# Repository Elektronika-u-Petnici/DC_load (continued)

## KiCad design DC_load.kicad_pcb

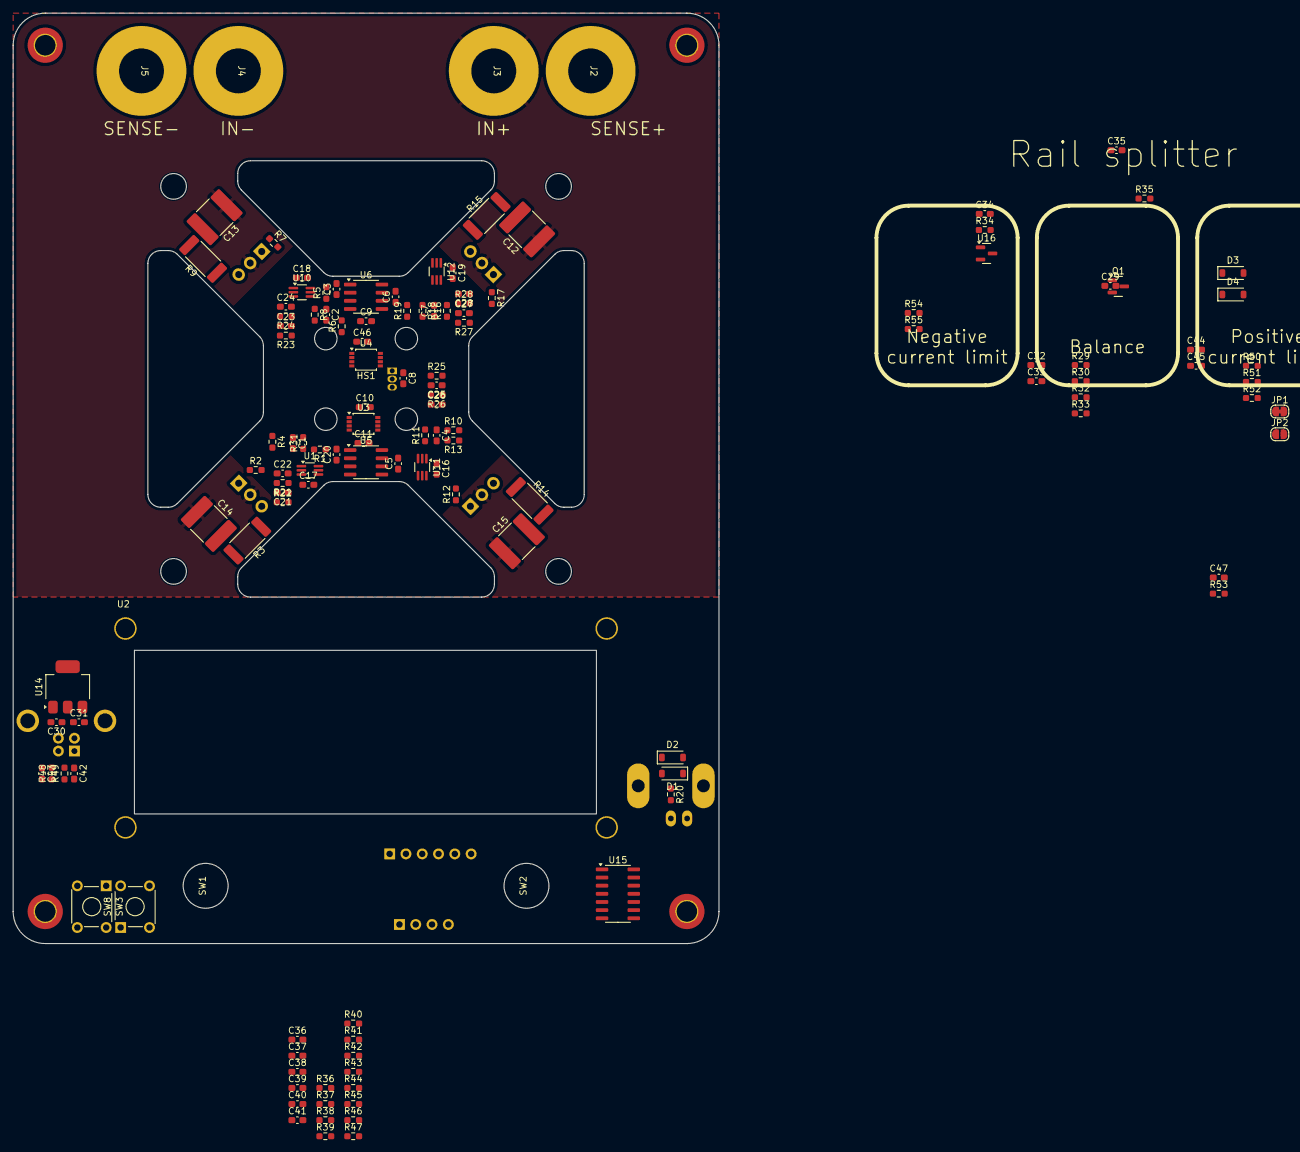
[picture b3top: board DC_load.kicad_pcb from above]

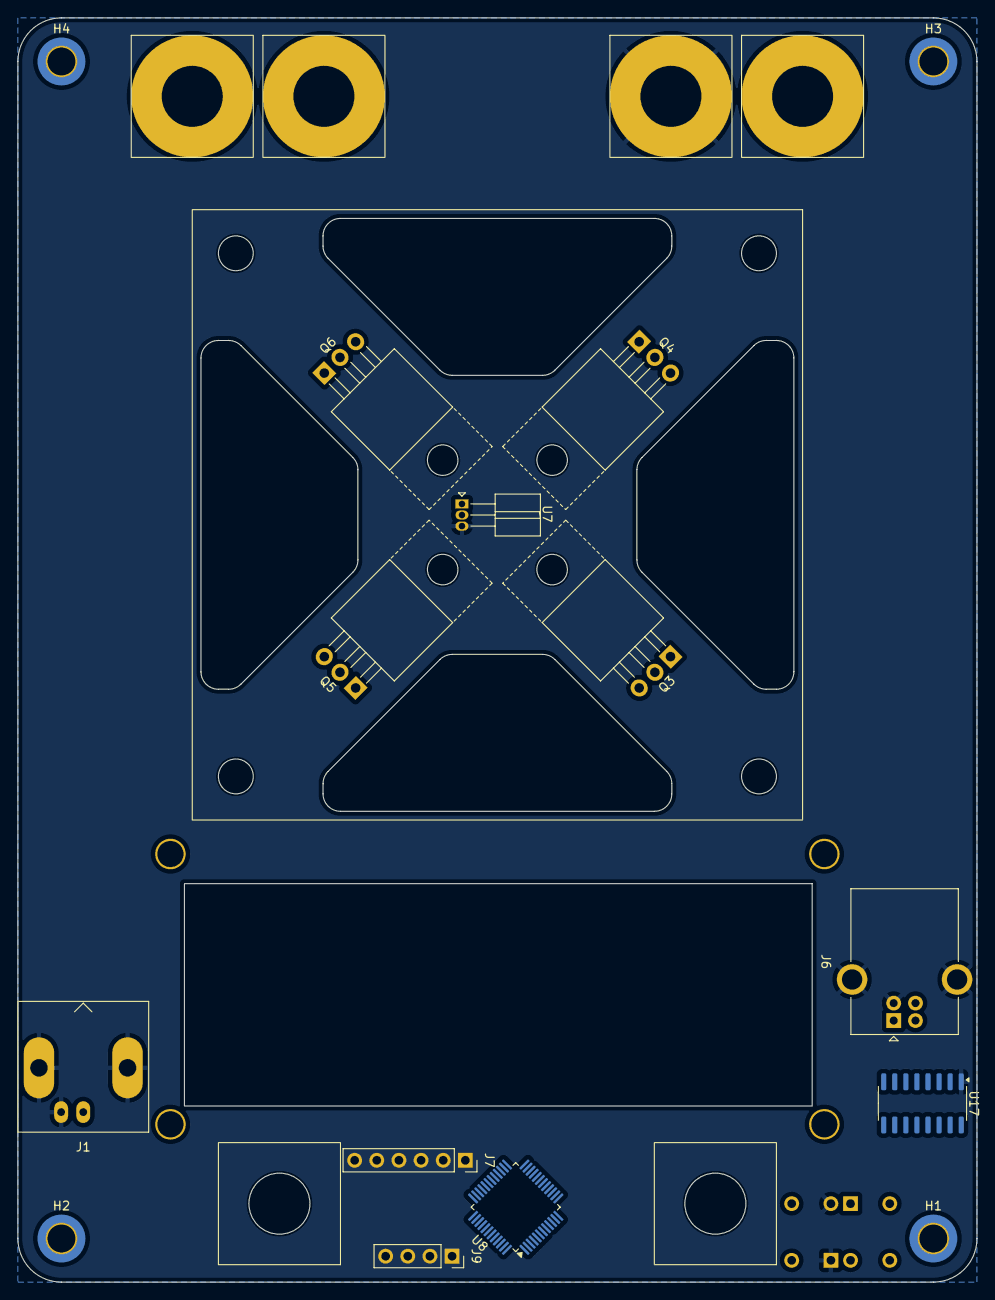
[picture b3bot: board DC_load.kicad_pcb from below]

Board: 2 copper layers, 110.0 x 145.0 mm, 145 parts (15 on the bottom side), 87 nets, no tracks yet.

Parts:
C1, C2, C3, C4, C5, C6, C7, C20, C22, C24, C26, C28: 100p; C_0603_1608Metric_Pad1.08x0.95mm_HandSolder
C8, C9, C10, C11, C16, C17, C18, C19, C29, C32, C33, C36, C39, C45, C46, C47: 100n; C_0603_1608Metric_Pad1.08x0.95mm_HandSolder
C12, C13, C14, C15: 1u; C_2220_5750Metric_Pad1.97x5.40mm_HandSolder
C21, C23, C25, C27, C37, C38, C40, C41, C44: 10n; C_0603_1608Metric_Pad1.08x0.95mm_HandSolder
C30, C31, C34, C35: 10u; C_0603_1608Metric_Pad1.08x0.95mm_HandSolder
C42, C43: 47p; C_0603_1608Metric_Pad1.08x0.95mm_HandSolder
D1, D2, D3, D4: 1N4148W; D_SOD-123
H1, H2, H3, H4: MountingHole; M3_hole_with_spacer
HS1: Heatsink; AMD_heatsink
J1: Conn_Coaxial; BNC_Amphenol_B6252HB-NPP3G-50_Horizontal
J2: red_terminal; 4mm_terminal_red
J3: red terminal; 4mm_terminal_red
J4, J5: black terminal; 4mm_terminal_black
J6: USB_B; USB_B_OST_USB-B1HSxx_Horizontal
J7: Conn_01x06_Socket; PinSocket_1x06_P2.54mm_Vertical
J9: Conn_01x04_Socket; PinSocket_1x04_P2.54mm_Vertical
JP1: Jumper_2_Bridged; SolderJumper-2_P1.3mm_Bridged_RoundedPad1.0x1.5mm
JP2: Jumper_2_Open; SolderJumper-2_P1.3mm_Open_RoundedPad1.0x1.5mm
Q1: MMBT5401; SOT-23
Q3, Q4, Q5, Q6: FQP19N20C; TO-220-3_Horizontal_TabUp
R1, R2, R7, R8, R12, R13, R16, R17, R20, R22, R23, R25, R27, R34, R35, R50, R52: 100; R_0603_1608Metric_Pad0.98x0.95mm_HandSolder
R3, R9, R14, R15: 10 mOhm; R_2512_6332Metric_Pad1.40x3.35mm_HandSolder
R4, R5, R6, R10, R11, R18, R19, R21, R24, R26, R28, R31, R36, R37, R39, R41, R43, R45, R51, R53, R54, R55: 10k; R_0603_1608Metric_Pad0.98x0.95mm_HandSolder
R29, R32: 1Meg; R_0603_1608Metric_Pad0.98x0.95mm_HandSolder
R30, R33: 50k; R_0603_1608Metric_Pad0.98x0.95mm_HandSolder
R38, R40, R42, R44, R46, R47: 100k; R_0603_1608Metric_Pad0.98x0.95mm_HandSolder
R48, R49: 22; R_0603_1608Metric_Pad0.98x0.95mm_HandSolder
SW1, SW2: RotaryEncoder_Switch; rotary_encoder_bottom_solder
SW3, SW8: SW_Push; SW_TH_Tactile_Omron_B3F-10xx
U1, U10, U11, U12: FSA3157P6X; SOT-363_SC-70-6_Handsoldering
U2: Screen; WC1602A - below
U3, U4: NCS21802; OnSemi_Micro8
U5, U6: TLV9062; SOIC-8_3.9x4.9mm_P1.27mm
U7: LMT84LPM; TO-92_Inline_W4.0mm_Horizontal_FlatSideUp
U8: STM32F103C8Tx; LQFP-48_7x7mm_P0.5mm
U14: AMS1117-3.3; SOT-223-3_TabPin2
U15: 74HC14D653; SOIC-14_3.9x8.7mm_P1.27mm
U16: LM4040DBZ-3; SOT-23
U17: CH340C; SOIC-16_3.9x9.9mm_P1.27mm

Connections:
3V3: C9.2, C29.2, C30.1, C46.2, D2.1 (K), JP2.2 (B), U3.8 (V+), U4.8 (V+), U8.1 (VBAT), U8.24 (VDD), U8.36 (VDD), U8.48 (VDD), U14.2 (VO), U17.16 (VCC)
5V: C10.2, C11.2, C16.2, C17.2, C18.2, C19.2, U1.5 (V+), U5.8 (V+), U6.8 (V+), U10.5 (V+), U11.5 (V+), U12.5 (V+)
+3V3: J7.4, J9.2, R36.1, R37.1, R39.1, R41.1, R43.1, R45.1, R51.1, R54.1, R55.1, SW3.2
+5V: C8.1, C31.1, D4.2 (A), J6.1 (VBUS), R34.2, R35.2, U7.1 (+V_{S}), U14.3 (VI)
/Microcontroller/BNC_CONTROL: D1.1 (K), D2.2 (A), R20.1, U1.1, U10.1, U11.1, U12.1
/Microcontroller/CH1_MEAS: C20.1, R4.2, U5.2 (-), U8.10 (PA0)
/Microcontroller/CH2_MEAS: C2.1, R5.1, R6.2, U4.1, U8.11 (PA1)
/Microcontroller/CH3_MEAS: C5.1, R10.2, U5.6 (-), U8.14 (PA4)
/Microcontroller/CH4_MEAS: C7.1, R18.2, R19.1, U4.7, U8.18 (PB0)
/Microcontroller/TX2: R52.2, U8.12 (PA2)
/Power_stage/V_SENSE+: J2.1, R29.2
/Power_stage/V_SENSE-: J5.1, R32.2
BOOT: C47.2, R53.1, SW3.1, U8.44 (BOOT0)
CH1_CONTROL: U1.4, U5.3 (+)
CH1_PWM: U8.29 (PA8), U15.9
CH2_CONTROL: U6.3 (+), U10.4
CH2_PWM: U8.38 (PA15), U15.11
CH3_CONTROL: U5.5 (+), U11.4
CH3_PWM: U8.16 (PA6), U15.13
CH4_CONTROL: U6.5 (+), U12.4
CH4_PWM: U8.17 (PA7), U15.1
CTRL_SEL: U1.6, U10.6, U11.6, U12.6
ENC_A_1: C40.2, R44.2
ENC_A_2: C37.2, R40.2
ENC_B_1: C41.2, R47.2
ENC_B_2: C38.2, R46.2
ENC_SW_1: C39.2, R42.2
ENC_SW_2: C36.2, R38.2
GND: C8.2, C9.1, C10.1, C11.1, C12.2, C13.2, C14.2, C15.2, C16.1, C17.1, C18.1, C19.1, C21.1, C22.1, C23.1, C24.1, C25.1, C26.1, C27.1, C28.1, C29.1, C30.2, C31.2, C32.1, C33.1, C34.2, C35.2, C36.1, C37.1, C38.1, C39.1, C40.1, C41.1, C42.2, C43.2, C44.1, C45.1, C46.1, C47.1, D1.2 (A), J1.2 (Ext), J4.1, J6.4 (GND), J6.5 (Shield), J7.6, J9.1, R1.1, R3.2, R8.1, R9.2, R13.1, R14.2, R15.2, R16.1, R30.2, R53.2, SW8.1, U1.2 (GND), U3.4 (V-), U4.4 (V-), U5.4 (V-), U6.4 (V-), U7.3 (GND), U8.8 (VSSA), U8.23 (VSS), U8.35 (VSS), U8.47 (VSS), U10.2 (GND), U11.2 (GND), U12.2 (GND), U14.1 (GND), U15.3, U15.5, U15.7 (GND), U16.2 (A), U17.1 (GND)
INPUT_POWER: C12.1, C13.1, C14.1, C15.1, J3.1, Q3.2 (D), Q4.2 (D), Q5.2 (D), Q6.2 (D)
unnamed: C1.1, R4.1, R31.2, U3.1
unnamed: C3.2, R7.2, U6.1
unnamed: C4.1, R10.1, R11.2, U3.7
unnamed: C5.2, R12.2, U5.7
unnamed: C6.2, R17.2, U6.7
unnamed: C20.2, R2.2, U5.1
unnamed: C21.2, R21.2, R22.1
unnamed: C22.2, R21.1, U1.3
unnamed: C23.2, R23.1, R24.2
unnamed: C24.2, R24.1, U10.3
unnamed: C25.2, R25.1, R26.2
unnamed: C26.2, R26.1, U11.3
unnamed: C27.2, R27.1, R28.2
unnamed: C28.2, R28.1, U12.3
unnamed: D3.2 (A), D4.1 (K)
unnamed: C35.1, D3.1 (K), Q1.1 (B)
unnamed: J1.1 (In), R20.2
unnamed: C43.1, J6.3 (D+), R48.2
unnamed: C42.1, J6.2 (D-), R49.2
unnamed: C32.2, JP1.1 (A), JP2.1 (A), U15.14 (VCC)
unnamed: Q1.2 (E), R35.1
unnamed: Q3.1 (G), R2.1
unnamed: Q3.3 (S), R3.1, U3.3 (+)
unnamed: Q4.1 (G), R7.1
unnamed: Q4.3 (S), R9.1, U4.3 (+)
unnamed: Q5.1 (G), R12.1
unnamed: Q5.3 (S), R14.1, U3.5 (+)
unnamed: Q6.1 (G), R17.1
unnamed: Q6.3 (S), R15.1, U4.5 (+)
unnamed: R22.2, U15.8
unnamed: R23.2, U15.10
unnamed: R25.2, U15.12
unnamed: R27.2, U15.2
unnamed: R36.2, R42.1
unnamed: R37.2, R38.1
unnamed: R39.2, R40.1
unnamed: R41.2, R46.1
unnamed: R43.2, R44.1
unnamed: R45.2, R47.1
unnamed: C1.2, R1.2, R31.1, U3.2 (-)
unnamed: C4.2, R11.1, R13.2, U3.6 (-)
unnamed: C2.2, R6.1, R8.2, U4.2 (-)
unnamed: C7.2, R16.2, R18.1, U4.6 (-)
unnamed: C3.1, R5.2, U6.2 (-)
unnamed: C6.1, R19.2, U6.6 (-)
unnamed: R29.1, R30.1
unnamed: R32.1, R33.2
unnamed: R50.2, U17.2 (TXD)
unnamed: R48.1, U17.5 (UD+)
unnamed: R49.1, U17.6 (UD-)
unnamed: C44.2, U17.4 (V3)
RESET: C45.2, R51.2, SW8.2, U8.7 (NRST)
RX: J7.2, R52.1, U8.30 (PA9), U17.3 (RXD)
SCL: J9.4, R55.2, U8.42 (PB6)
SDA: J9.3, R54.2, U8.43 (PB7)
TX: J7.3, R50.1, U8.13 (PA3), U8.31 (PA10)
VREF: C33.2, C34.1, JP1.2 (B), Q1.3 (C), R34.1, U8.9 (VDDA), U16.1 (K)

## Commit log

2025-11-20 Init.
2025-11-20 Added readme.
2025-11-24 New dimensions.
2025-11-24 Schematic progress.
2025-11-25 aesthetics.
2025-11-26 Schematic and placement update.
2025-11-26 Added front plate.
2025-11-27 Compressed.
2025-11-27 Most routing done.
2025-11-27 Added EEPROM
2025-11-27 MCU almost routed.
2025-11-27 MIddle.
2025-11-27 kldsjfald.
2025-11-27 sdaf
2025-11-28 Getting closer.
2025-11-28 No errors.
2025-11-28 All cool
2025-11-28 Added voltage sense
2025-11-28 aethetics.
2025-11-28 Fan black now.
2025-11-28 note.
2025-11-30 DC fan boost converter added.
2025-11-30 Done.
2025-11-30 No errors, fan added.
2025-11-30 Review left.
2025-11-30 Added jumper.
2025-11-30 More agresive PWM filtering.
2025-12-01 Vbe multiplier, constant current source 12V mosfet gate driver. RC filters moved lower. INA181 for 20x gain, 50 mOhm shunts. Jumper moved to BNC. Rough placement initiated.
2025-12-01 Još gate driver layout.
2025-12-02 RC filter na ADC linijama Placement update.
2025-12-02 Done???.
2025-12-02 Ready for production.
2025-12-04 Galvanic isolation for the UART.
2025-12-07 MC to 12V -> halfbridge to rest.
2025-12-08 Sim, comp, power.
2025-12-08 Idk.
2025-12-10 Schematic done.
2025-12-11 Some placement.
2025-12-11 lay.
2025-12-17 Replaced switches with JLCPCB basic.
2025-12-17 Schem Schem.
2025-12-24 SRF sch.
2025-12-24 SRF layout
2025-12-28 Working on layout.
2025-12-28 Routing.
2026-01-10 Connectors fixed.
2026-01-11 Tiny update.
2026-01-11 Main board close to done.
2026-01-11 Iso module almost done.
2026-01-11 sdf.
2026-01-16 Fixes
2026-01-17 kfsald
2026-01-17 pre prod
